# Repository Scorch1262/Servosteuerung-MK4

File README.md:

# Servosteuerung-MK4

3D-Druck Daten:
https://makerworld.com/de/models/1615042-servo-control-mk4

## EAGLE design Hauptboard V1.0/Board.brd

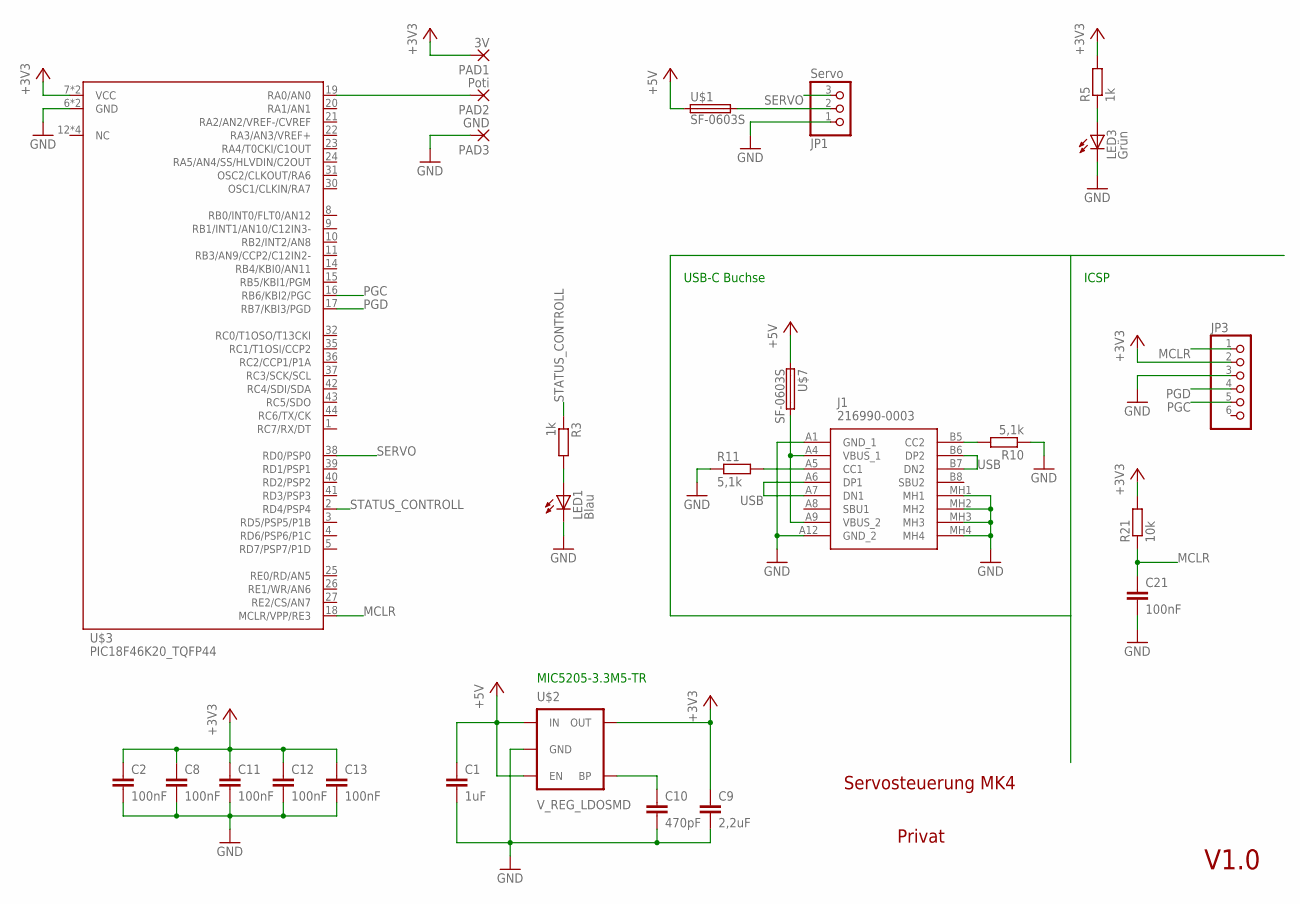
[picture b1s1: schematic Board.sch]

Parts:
C1: 1uF; C0805
C2, C8, C11, C12, C13, C21: 100nF; C0805
C9: 2,2uF; C0805
C10: 470pF; C0805
J1: 216990-0003; 2169900003
JP1: Servo; 1X03/90
JP3: PINHD-1X6; 1X06
LED1: Blau; CHIPLED_0805
LED3: Grün; CHIPLED_0805
PAD1: 3V; 5-1,8_50
PAD2: Poti; 5-1,8_50
PAD3: GND; 5-1,8_50
R3, R5: 1k; R0805
R10, R11: 5,1k; R0805
R21: 10k; R0805
U$1, U$7: SF-0603S; R0603
U$2: V_REG_LDOSMD; SOT23-5
U$3: PIC18F46K20_TQFP44; TQFP44

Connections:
+3V3: C2.1, C8.1, C9.1, C11.1, C12.1, C13.1, JP3.2, PAD1.1, R5.2, R21.2, U$2.5 (OUT), U$3.7 (VCC), U$3.28 (VCC)
+5V: C1.1, U$1.1, U$2.1 (IN), U$2.3 (EN), U$7.1
GND: C1.2, C2.2, C8.2, C9.2, C10.2, C11.2, C12.2, C13.2, C21.2, J1.A1 (GND_1), J1.A12 (GND_2), J1.MH1, J1.MH2, J1.MH3, J1.MH4, JP1.1, JP3.3, LED1.C, LED3.C, PAD3.1, R10.1, R11.1, U$2.2 (GND), U$3.6 (GND), U$3.29 (GND)
MCLR: C21.1, JP3.1, R21.1, U$3.18 (MCLR/VPP/RE3)
unnamed: PAD2.1, U$3.19 (RA0/AN0)
unnamed: JP1.2, U$1.2
unnamed: LED3.A, R5.1
unnamed: LED1.A, R3.2
unnamed: C10.1, U$2.4 (BP)
unnamed: J1.A4 (VBUS_1), J1.A9 (VBUS_2), U$7.2
unnamed: J1.A5 (CC1), R11.2
unnamed: J1.B5 (CC2), R10.2
PGC: JP3.5, U$3.16 (RB6/KBI2/PGC)
PGD: JP3.4, U$3.17 (RB7/KBI3/PGD)
SERVO: JP1.3, U$3.38 (RD0/PSP0)
STATUS_CONTROLL: R3.1, U$3.2 (RD4/PSP4)
USB: J1.A6 (DP1), J1.A7 (DN1), J1.B6 (DP2), J1.B7 (DN2)

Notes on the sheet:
Servosteuerung MK4
Privat
V1.0
ICSP
MIC5205-3.3M5-TR
USB-C Buchse

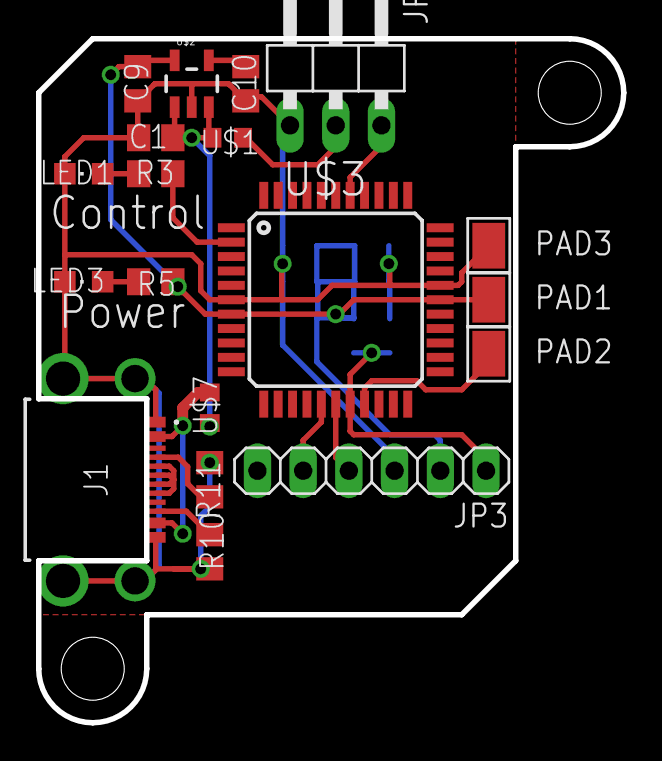
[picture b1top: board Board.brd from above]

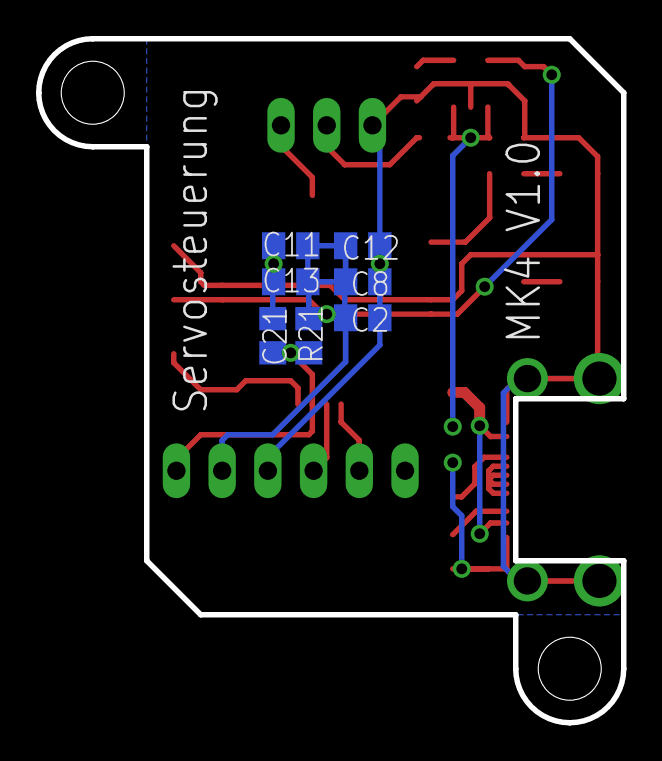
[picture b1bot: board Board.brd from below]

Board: 2 copper layers, 32.5 x 38.0 mm, 26 parts (7 on the bottom side), 17 nets.

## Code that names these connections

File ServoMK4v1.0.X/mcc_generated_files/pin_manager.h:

/**
  @Generated Pin Manager Header File

  @Company:
    Microchip Technology Inc.

  @File Name:
    pin_manager.h

  @Summary:
    This is the Pin Manager file generated using PIC10 / PIC12 / PIC16 / PIC18 MCUs

  @Description
    This header file provides APIs for driver for .
    Generation Information :
        Product Revision  :  PIC10 / PIC12 / PIC16 / PIC18 MCUs - 1.81.7
        Device            :  PIC18F46K20
        Driver Version    :  2.11
    The generated drivers are tested against the following:
        Compiler          :  XC8 2.31 and above
        MPLAB 	          :  MPLAB X 5.45	
*/

/*
    (c) 2018 Microchip Technology Inc. and its subsidiaries. 
    
    Subject to your compliance with these terms, you may use Microchip software and any 
    derivatives exclusively with Microchip products. It is your responsibility to comply with third party 
    license terms applicable to your use of third party software (including open source software) that 
    may accompany Microchip software.
    
    THIS SOFTWARE IS SUPPLIED BY MICROCHIP "AS IS". NO WARRANTIES, WHETHER 
    EXPRESS, IMPLIED OR STATUTORY, APPLY TO THIS SOFTWARE, INCLUDING ANY 
    IMPLIED WARRANTIES OF NON-INFRINGEMENT, MERCHANTABILITY, AND FITNESS 
    FOR A PARTICULAR PURPOSE.
    
    IN NO EVENT WILL MICROCHIP BE LIABLE FOR ANY INDIRECT, SPECIAL, PUNITIVE, 
    INCIDENTAL OR CONSEQUENTIAL LOSS, DAMAGE, COST OR EXPENSE OF ANY KIND 
    WHATSOEVER RELATED TO THE SOFTWARE, HOWEVER CAUSED, EVEN IF MICROCHIP 
    HAS BEEN ADVISED OF THE POSSIBILITY OR THE DAMAGES ARE FORESEEABLE. TO 
    THE FULLEST EXTENT ALLOWED BY LAW, MICROCHIP'S TOTAL LIABILITY ON ALL 
    CLAIMS IN ANY WAY RELATED TO THIS SOFTWARE WILL NOT EXCEED THE AMOUNT 
    OF FEES, IF ANY, THAT YOU HAVE PAID DIRECTLY TO MICROCHIP FOR THIS 
    SOFTWARE.
*/

#ifndef PIN_MANAGER_H
#define PIN_MANAGER_H

/**
  Section: Included Files
*/

#include <xc.h>

#define INPUT   1
#define OUTPUT  0

#define HIGH    1
#define LOW     0

#define ANALOG      1
#define DIGITAL     0

#define PULL_UP_ENABLED      1
#define PULL_UP_DISABLED     0

// get/set ADC aliases
#define ADC_TRIS                 TRISAbits.TRISA0
#define ADC_LAT                  LATAbits.LATA0
#define ADC_PORT                 PORTAbits.RA0
#define ADC_ANS                  ANSELbits.ANS0
#define ADC_SetHigh()            do { LATAbits.LATA0 = 1; } while(0)
#define ADC_SetLow()             do { LATAbits.LATA0 = 0; } while(0)
#define ADC_Toggle()             do { LATAbits.LATA0 = ~LATAbits.LATA0; } while(0)
#define ADC_GetValue()           PORTAbits.RA0
#define ADC_SetDigitalInput()    do { TRISAbits.TRISA0 = 1; } while(0)
#define ADC_SetDigitalOutput()   do { TRISAbits.TRISA0 = 0; } while(0)
#define ADC_SetAnalogMode()      do { ANSELbits.ANS0 = 1; } while(0)
#define ADC_SetDigitalMode()     do { ANSELbits.ANS0 = 0; } while(0)

// get/set Servo aliases
#define Servo_TRIS                 TRISDbits.TRISD0
#define Servo_LAT                  LATDbits.LATD0
#define Servo_PORT                 PORTDbits.RD0
#define Servo_SetHigh()            do { LATDbits.LATD0 = 1; } while(0)
#define Servo_SetLow()             do { LATDbits.LATD0 = 0; } while(0)
#define Servo_Toggle()             do { LATDbits.LATD0 = ~LATDbits.LATD0; } while(0)
#define Servo_GetValue()           PORTDbits.RD0
#define Servo_SetDigitalInput()    do { TRISDbits.TRISD0 = 1; } while(0)
#define Servo_SetDigitalOutput()   do { TRISDbits.TRISD0 = 0; } while(0)

// get/set Status_Controll aliases
#define Status_Controll_TRIS                 TRISDbits.TRISD4
#define Status_Controll_LAT                  LATDbits.LATD4
#define Status_Controll_PORT                 PORTDbits.RD4
#define Status_Controll_SetHigh()            do { LATDbits.LATD4 = 1; } while(0)
#define Status_Controll_SetLow()             do { LATDbits.LATD4 = 0; } while(0)
#define Status_Controll_Toggle()             do { LATDbits.LATD4 = ~LATDbits.LATD4; } while(0)
#define Status_Controll_GetValue()           PORTDbits.RD4
#define Status_Controll_SetDigitalInput()    do { TRISDbits.TRISD4 = 1; } while(0)
#define Status_Controll_SetDigitalOutput()   do { TRISDbits.TRISD4 = 0; } while(0)

/**
   @Param
    none
   @Returns
    none
   @Description
    GPIO and peripheral I/O initialization
   @Example
    PIN_MANAGER_Initialize();
 */
void PIN_MANAGER_Initialize (void);

/**
 * @Param
    none
 * @Returns
    none
 * @Description
    Interrupt on Change Handling routine
 * @Example
    PIN_MANAGER_IOC();
 */
void PIN_MANAGER_IOC(void);



#endif // PIN_MANAGER_H
/**
 End of File
*/

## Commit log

2025-07-17 upload
